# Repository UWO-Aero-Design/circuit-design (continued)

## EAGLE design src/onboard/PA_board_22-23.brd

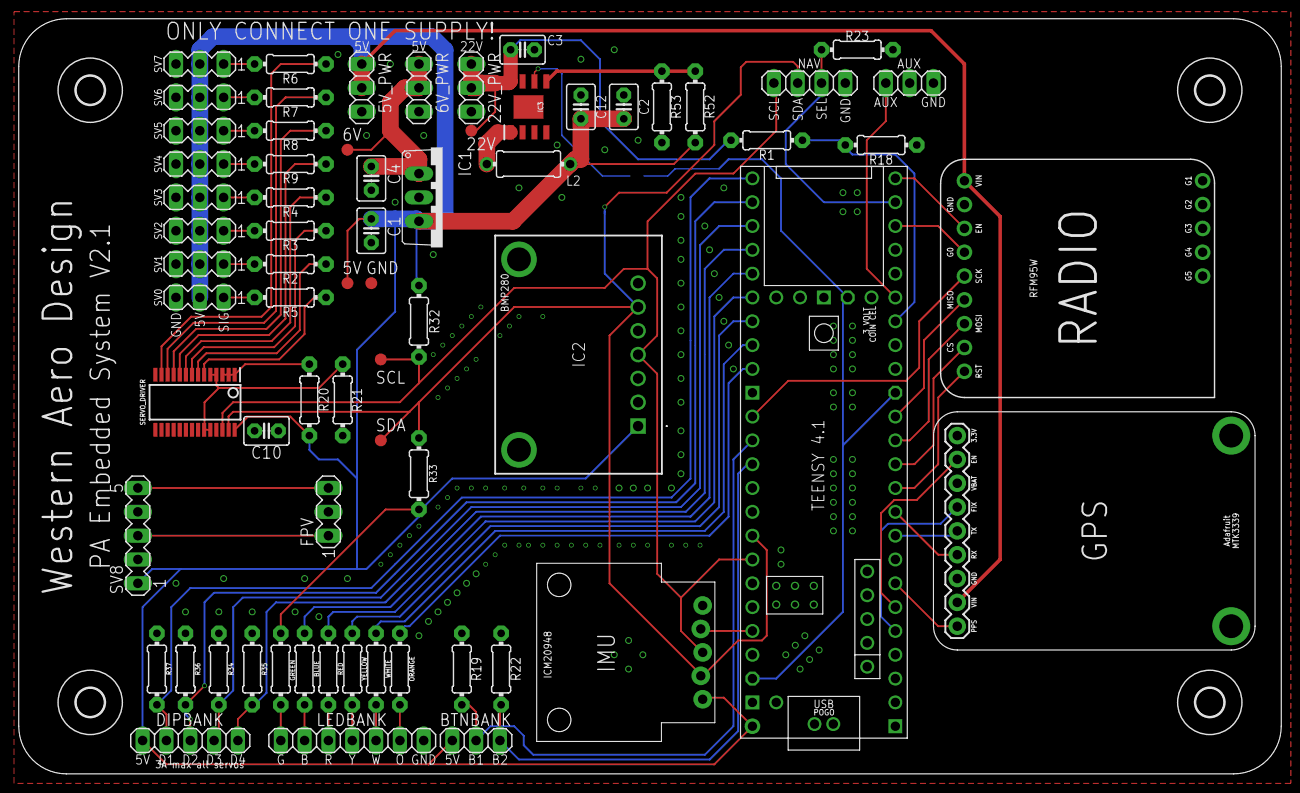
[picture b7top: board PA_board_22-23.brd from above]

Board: 2 copper layers, 134.6 x 80.5 mm, 73 parts (1 on the bottom side), 62 nets.

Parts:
5V, 6V, 22V: PTR1B1,27; B1,27
5V_PWR: 5V_PWR; 1X03
6V_PWR: 6V_PWR; 1X03
22V_PWR: 22V_PWR; 1X03
AUX: 1X03
BLUE: 80; 0204/7
BTNBANK: 1X03
C1, C2, C3, C4, C10: 10uF; C2.5-3
C12: 470uF; C2.5-3
DIPBANK: 1X05
FPV: MA03-1
GND: PTR1B1,27; B1,27
GPSMTK3339: ADAFRUIT_MTK3339_GPS
GREEN: 150; 0204/7
IC1: MIC29310-5.0BT; TO220V
IC2: ADAFRUIT_BMP280; ADAFRUITBMP280
IC3: A5975D; SOIC127P600X170-9N
IMU: ICM20948BREAKOUTDEVICE; ICM20948BREAKOUT
L2: 27uH; TFI0307
LEDBANK: 1X07
NAV: 1X04
ORANGE: 150; 0204/7
R1: 1.8M; 0204/7
R2, R3, R4, R5, R6, R7, R8, R9: 220; 0204/7
R18: 430k; 0204/7
R19, R22, R23, R34, R35, R36, R37: 2.2k; 0204/7
R20, R21: 10K; 0204/7
R32, R33: 4.7k; 0204/7
R52: 1k; 0204/7
R53: 3k; 0204/7
RADIO: ADAFRUIT_RFM95W_LORA_RADIO
RED: 150; 0204/7
SCL: PTR1B1,27; B1,27
SDA: PTR1B1,27; B1,27
SERVO_DRIVER: PCA9685PW,112; SOP65P640X110-28N
SJ1: SJ
SV0, SV1, SV2, SV3, SV4, SV5, SV6, SV7: MA03-1
SV8: MA05-1
TEENSY4.1: TEENSY41
U$1, U$2, U$3, U$4: 3,0
WHITE: 90; 0204/7
YELLOW: 150; 0204/7

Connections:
3.3V: SJ1.2, TEENSY4.1.3V3-1, TEENSY4.1.3V3-2, TEENSY4.1.3V3-3
5V: 5V.TP, 5V_PWR.1, 5V_PWR.2, BTNBANK.3, C1.1, C2.1, C10.1, C12.1, DIPBANK.5, FPV.1, GPSMTK3339.VIN, GREEN.1, IC1.3, IC2.1, IMU.2-6V, L2.1, R20.2, R32.2, R33.2, R52.2, RADIO.1, SERVO_DRIVER.28, SV0.2, SV1.2, SV2.2, SV3.2, SV4.2, SV5.2, SV6.2, SV7.2, SV8.1, SV8.3, TEENSY4.1.VIN
6V: 6V.TP, 6V_PWR.1, 6V_PWR.2, C4.1, IC1.1
22V_INPUT: 22V.TP, 22V_PWR.1, 22V_PWR.2, C3.1, IC3.8, R1.2
AUX: AUX.3, TEENSY4.1.27-A13/SCK1
BATLEVEL: R1.1, R18.2, TEENSY4.1.26-A12/MOSI1
BLUE: BLUE.2, LEDBANK.6
BTN1: BTNBANK.2, R19.2, TEENSY4.1.14-A0/TX3/SPDIF_OUT
BTN2: BTNBANK.1, R22.2, TEENSY4.1.15-A1/RX3/SPDIF_IN
B_LED: BLUE.1, TEENSY4.1.37-PWM
CS0: RADIO.8, TEENSY4.1.10-CS\MQSR
DIP1: DIPBANK.4, R37.2, TEENSY4.1.33-MCLK2
DIP2: DIPBANK.3, R36.2, TEENSY4.1.34-RX8
DIP3: DIPBANK.2, R34.2, TEENSY4.1.35-TX8
DIP4: DIPBANK.1, R35.2, TEENSY4.1.36-PWM
GND: 5V_PWR.3, 6V_PWR.3, 22V_PWR.3, AUX.1, C1.2, C2.2, C3.2, C4.2, C10.2, C12.2, FPV.2, GND.TP, GPSMTK3339.GND, IC1.2, IC2.3, IC3.3, IC3.7, IMU.GND, LEDBANK.1, NAV.1, R18.1, R19.1, R21.1, R22.1, R23.1, R34.1, R35.1, R36.1, R37.1, R53.1, RADIO.2, SERVO_DRIVER.14, SERVO_DRIVER.25, SV0.3, SV1.3, SV2.3, SV3.3, SV4.3, SV5.3, SV6.3, SV7.3, SV8.2, SV8.4, TEENSY4.1.GND1, TEENSY4.1.GND2, TEENSY4.1.GND3, TEENSY4.1.GND4, TEENSY4.1.GND5, TEENSY4.1.GND6
GNDADDRESS: R21.2, SERVO_DRIVER.4, SERVO_DRIVER.5, SERVO_DRIVER.23, SERVO_DRIVER.24
GPS_EN: GPSMTK3339.EN, TEENSY4.1.4-BCLK2
GPS_FIX: GPSMTK3339.FIX, TEENSY4.1.3-LRCLK2
GPS_PPS: GPSMTK3339.PPS, TEENSY4.1.5-IN2
GREEN: GREEN.2, LEDBANK.7
IMU_INT: IMU.INT, TEENSY4.1.22-A8/CTX1
MISO0: RADIO.6, TEENSY4.1.12-MISO/MQSL
MOSI0: RADIO.7, TEENSY4.1.11-MOSI/CTX1
unnamed: R20.1, SERVO_DRIVER.1, SERVO_DRIVER.2, SERVO_DRIVER.3
unnamed: IC3.6, SJ1.1
unnamed: IC3.1, L2.2
unnamed: IC3.5, R52.1, R53.2
unnamed: R6.2, SV7.1
unnamed: R4.2, SV3.1
unnamed: R3.2, SV2.1
unnamed: R7.2, SV6.1
unnamed: R2.2, SV1.1
unnamed: R5.2, SV0.1
unnamed: R9.2, SV4.1
unnamed: R8.2, SV5.1
ORANGE: LEDBANK.2, ORANGE.2
O_LED: ORANGE.1, TEENSY4.1.41-A17/MISO1
PWM0: R5.1, SERVO_DRIVER.6
PWM1: R2.1, SERVO_DRIVER.7
PWM2: R3.1, SERVO_DRIVER.8
PWM3: R4.1, SERVO_DRIVER.9
PWM4: R9.1, SERVO_DRIVER.10
PWM5: R8.1, SERVO_DRIVER.11
PWM6: R7.1, SERVO_DRIVER.12
PWM7: R6.1, SERVO_DRIVER.13
RADIO_EN: RADIO.3, TEENSY4.1.32-OUT1B
RADIO_INT: RADIO.4, TEENSY4.1.30-CRX3
RADIO_RST: RADIO.9, TEENSY4.1.9-OUT1C
RED: LEDBANK.5, RED.2
RX2: GPSMTK3339.TX, TEENSY4.1.7-RX2/OUT1A
R_LED: RED.1, TEENSY4.1.38-A14/CS/IN1
SCK0: RADIO.5, TEENSY4.1.13-SCK/LED
SCL: IC2.4, IMU.SCL, NAV.4, R32.1, SCL.TP, SERVO_DRIVER.26, TEENSY4.1.19-A5/SCL0
SDA: IC2.6, IMU.SDA, NAV.3, R33.1, SDA.TP, SERVO_DRIVER.27, TEENSY4.1.18-A4/SDA0
SELECT_PIN: NAV.2, R23.2, TEENSY4.1.31-CTX3
TX2: GPSMTK3339.RX, TEENSY4.1.8-TX2/IN1
VIDEO: FPV.3, SV8.5
WHITE: LEDBANK.3, WHITE.2
W_LED: TEENSY4.1.40-A16/CS1, WHITE.1
YELLOW: LEDBANK.4, YELLOW.2
Y_LED: TEENSY4.1.39-A15/CS/OUT1A, YELLOW.1
